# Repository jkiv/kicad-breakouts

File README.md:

# kicad-breakouts

This project contains various breadboard-compatible breakouts for testing and educational purposes.

## Breakouts

### Active Projects

| Device | Manufacturer | Folder | Status | External Links |
| --- | --- | --- | --- | --- |
| ICE40HX8K (caBGA-121) | Lattice | `/boards/ice40hx8k-bg121` | In development... | [[1]](http://www.latticesemi.com/iCE40) |
| LFE5U-* (csBGA-285) | Lattice | `/boards/ecp5-stamp` | In development... | [[2]](http://www.latticesemi.com/ECP5) |
| FT2232H | FTDI | `/boards/ft2232h-ice40` | In development... | [[3]](https://www.ftdichip.com/Products/ICs/FT2232H.htm) |
| ATSAMD21E18A | Atmel | `/boards/atsamd21e18a` | In development... | [[4]](https://www.microchip.com/wwwproducts/en/ATsamd21e18) |

## Dependencies

This project depends on the following KiCad libraries:

* [Digi-Key/digikey-kicad-library](https://github.com/Digi-Key/digikey-kicad-library)
* [jkiv/jkiv-kicad-library](https://github.com/jkiv/jkiv-kicad-library)
* [xesscorp/KiCad-Schematic-Symbol-Libraries](https://github.com/xesscorp/KiCad-Schematic-Symbol-Libraries)

These repositories are set up as git submodules and can be cloned into `hardware/external/` using the following two commands:

    $ git submodule init
    $ git submodule update

## Donations 

Help support this project and others like it by donating:

* XBT: 13zRrs1YDdooUN5WtfXRSDn8KnJdok4qG9

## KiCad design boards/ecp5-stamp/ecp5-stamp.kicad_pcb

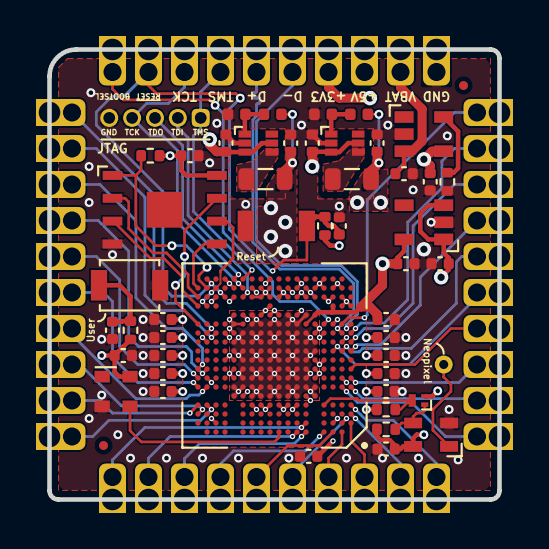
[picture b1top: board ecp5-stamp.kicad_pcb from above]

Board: 4 copper layers, 25.0 x 25.0 mm, 55 parts (0 on the bottom side), 60 nets.

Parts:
C1, C2, C3, C4, C5, C6, C7, C8, C9, C10, C17, C18, C19, C21, C23, C24: 0.1u; C_0402_1005Metric
C11, C12, C13, C14, C20, C22: 4u7; C_0402_1005Metric
C15: 22u; C_0402_1005Metric
C16: 10u; C_0402_1005Metric
D1: SK6805 EC 15; LED_SK6805_PLCC4_2.4x2.7mm_P1.3mm
FID1, FID2: Fiducial; Fiducial_0.5mm_Mask1mm
J1: West; PinHeader_1x10_P2.0mm_Castillated
J2: South; PinHeader_1x10_P2.0mm_Castillated
J3: East; PinHeader_1x10_P2.0mm_Castillated
J4: North; PinHeader_1x10_P2.0mm_Castillated
J5: JTAG; PinHeader_1x05_P1.27mm_Vertical
L1, L2: 2.2u; L_0805_2012Metric
Q1: DMN21D2UFB-7B; Diodes_DFN1006-3
R1, R6: 1k; R_0402_1005Metric
R2, R3: ?k; L_0402_1005Metric
R4, R5: ?; L_0402_1005Metric
R7: 2k; R_0402_1005Metric
R8, R9, R10: 4k7; R_0402_1005Metric
SW1: ~RESET; SW_SPST_B3U-1000P
SW2: ~USER; SW_SPST_B3U-1000P
TP1: NP_OUT; PinHeader_1x01_P1.00mm_Vertical
U1: W25Q128JVS; DFN-8-1EP_6x5mm_P1.27mm_EP2x2mm
U2: MCP73831-2-OT; SOT-23-5
U3: ECP5UM_25_CSFBGA285; BGA-324_18x18_10.0x10.0mm
U4: ASDMB-12.000MHz; Oscillator_SMD_Abracon_ASDMB-4Pin_2.5x2.0mm
U5: TLV73325PDBV; SOT-23-5
U6, U7: TLV62569DRL; SOT-563

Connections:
+1V1: C3.1, C4.1, C15.1, L1.2, R2.1, U3.D8, U3.D9, U3.D10, U3.D11, U3.J4, U3.J5, U3.J14, U3.J15, U3.M4, U3.M15, U3.P7, U3.P9, U3.P10, U3.P11, U3.R10, U3.T5, U3.U6, U3.U8, U3.U12
+2V5: C14.1, C23.1, C24.1, U3.E6, U3.E13, U3.N6, U3.P5, U3.P13, U3.R3, U5.5
+3V3: C2.1, C5.1, C6.1, C7.1, C8.1, C9.1, C10.1, C13.1, C16.1, C17.1, C18.1, J4.4, L2.2, Q1.2, R1.1, R4.1, R6.1, R8.1, R9.1, U1.8, U3.D7, U3.D12, U3.G5, U3.G14, U3.H5, U3.H14, U3.M5, U3.M14, U3.N5, U3.N13, U3.N14, U3.P14, U3.T14, U4.4, U5.1, U5.3
+5V: C11.1, C12.1, C20.1, C21.1, D1.4, J4.3, R10.1, U2.4, U6.3, U6.5, U7.3, U7.5
+BATT: C22.1, J4.2, U2.3
/BOOTSEL: J4.10, U3.N4
/FLASH_CS: R8.2, U1.1, U3.U17
/FLASH_IO0: U1.5, U3.U18
/FLASH_IO1: U1.2, U3.T18
/FLASH_IO2: U1.3, U3.R18
/FLASH_IO3: U1.7, U3.N18
/FLASH_SCK: U1.6, U3.R17, U3.U16
/GPIO_00: J1.1, U3.M17
/GPIO_01: J1.2, U3.M16
/GPIO_02: J1.3, U3.H18
/GPIO_03: J1.4, U3.H17
/GPIO_04: J1.5, U3.G18
/GPIO_05: J1.6, U3.F18
/GPIO_06: J1.7, U3.F17
/GPIO_07: J1.8, U3.C18
/GPIO_08: J1.9, U3.D18
/GPIO_09: J1.10, U3.D17
/GPIO_10: J2.1, U3.B6
/GPIO_11: J2.2, U3.A7
/GPIO_12: J2.3, U3.A6
/GPIO_13: J2.4, U3.A4
/GPIO_14: J2.5, U3.A3
/GPIO_15: J2.6, U3.B2
/GPIO_16: J2.7, U3.A2
/GPIO_17: J2.8, U3.B1
/GPIO_18: J2.9, U3.C1
/GPIO_19: J2.10, U3.D1
/GPIO_20: J3.1, U3.F2
/GPIO_21: J3.2, U3.F1
/GPIO_22: J3.3, U3.G1
/GPIO_23: J3.4, U3.H1
/GPIO_24: J3.5, U3.K3
/GPIO_25: J3.6, U3.K2
/GPIO_26: J3.7, U3.K1
/GPIO_27: J3.8, U3.L1
/GPIO_28: J3.9, U3.M1
/GPIO_29: J3.10, U3.N2
/JTAG_TCK: J4.8, J5.4, U3.U13
/JTAG_TDI: J5.2, U3.T13
/JTAG_TDO: J5.3, U3.V14
/JTAG_TMS: J4.7, J5.1, U3.V13
/NP_SDI: D1.3, Q1.1, R10.2
/NP_SDI_LV: Q1.3, R9.2, U3.D4
/NP_SDO: D1.1, TP1.1
/REF_CLK: U3.A9, U4.3
/SW_1V1: L1.1, U6.4
/SW_3V3: L2.1, U7.4
/USB_D+: J4.6, U3.M2
/USB_D-: J4.5, U3.N1
/~RESET: C1.1, J4.9, R1.2, SW1.2, U3.T15, U3.V17
/~USER: C19.1, R6.2, SW2.2
GND: C1.2, C2.2, C3.2, C4.2, C5.2, C6.2, C7.2, C8.2, C9.2, C10.2, C11.2, C12.2, C13.2, C14.2, C15.2, C16.2, C17.2, C18.2, C19.2, C20.2, C21.2, C22.2, C23.2, C24.2, D1.2, J4.1, J5.5, R3.2, R5.2, R7.2, SW1.1, SW2.1, U1.4, U2.2, U3.B3, U3.B16, U3.E5, U3.E7, U3.E8, U3.E9, U3.E10, U3.E11, U3.E12, U3.E14, U3.F5, U3.F6, U3.F7, U3.F8, U3.F9, U3.F10, U3.F11, U3.F12, U3.F13, U3.F14, U3.G2, U3.G6, U3.G7, U3.G8, U3.G9, U3.G10, U3.G11, U3.G12, U3.G13, U3.G17, U3.H6, U3.H7, U3.H8, U3.H9, U3.H10, U3.H11, U3.H12, U3.H13, U3.J6, U3.J7, U3.J8, U3.J9, U3.J10, U3.J11, U3.J12, U3.J13, U3.K5, U3.K6, U3.K7, U3.K8, U3.K9, U3.K10, U3.K11, U3.K12, U3.K13, U3.K14, U3.L2, U3.L5, U3.L6, U3.L7, U3.L8, U3.L9, U3.L10, U3.L11, U3.L12, U3.L13, U3.L14, U3.L17, U3.M6, U3.M7, U3.M8, U3.M9, U3.M10, U3.M11, U3.M12, U3.M13, U3.N7, U3.N8, U3.N9, U3.N10, U3.N11, U3.N12, U3.P6, U3.P8, U3.P12, U3.R1, U3.R2, U3.T2, U3.T3, U3.T4, U3.T6, U3.T7, U3.T8, U3.T9, U3.T10, U3.T11, U3.T12, U3.T16, U3.U2, U3.U3, U3.U4, U3.U5, U3.U7, U3.U9, U3.U10, U3.U11, U3.U14, U3.V4, U3.V7, U3.V10, U3.V15, U4.2, U5.2, U6.2, U7.2
unnamed: R2.2, R3.1, U6.1
unnamed: R4.2, R5.1, U7.1
unnamed: R7.1, U2.5

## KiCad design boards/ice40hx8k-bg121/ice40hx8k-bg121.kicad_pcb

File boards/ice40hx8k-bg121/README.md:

# ice40hx8k-bg121 Breakout Board

## About

This is a breadboardable breakout board for a Lattice iCE40HX8K FPGA.

* Four IO banks with 32 exposed IOs
  * 12 + 4 breadboardable IO
  * 8 + 8 IO via 2.54mm headers
  * Eight on-board LEDs (Bank D)
* Settable VIO for IO Banks A, B, and D.
* 12-pin PMOD compatible pinout for IO banks B and D.
* 6-pin PMOD compatible pinout for IO bank C.
* On-board 2Mbit flash memory.
* On-board 12MHz clock source.
* On-board reset button.

*This board does **not** contain programming circuitry. The [`ft2232h-ice40` breakout](https://github.com/jkiv/kicad-breakouts/tree/main/boards/ft2232h-ice40) is intended to provide the programming circuitry for this board.*

## Rationale

This board began with the intent to provide a breadboardable FPGA for educational purposes.

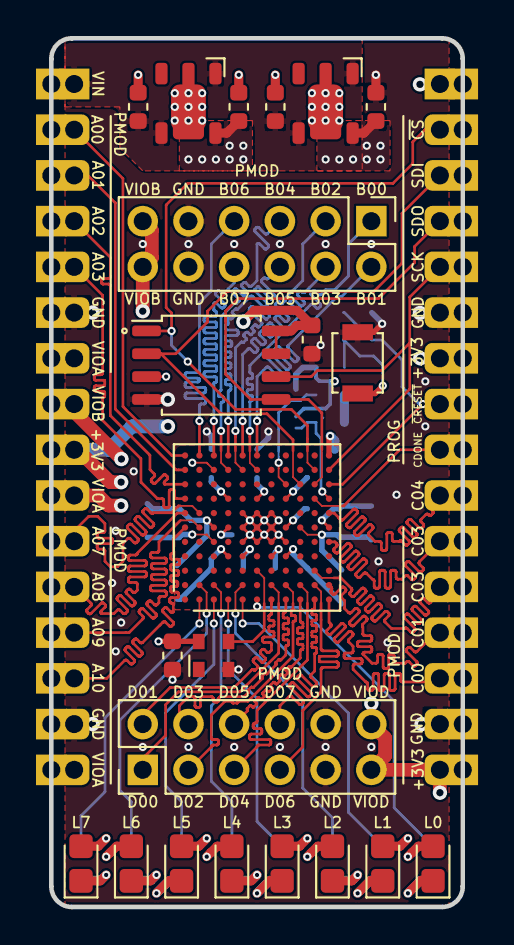
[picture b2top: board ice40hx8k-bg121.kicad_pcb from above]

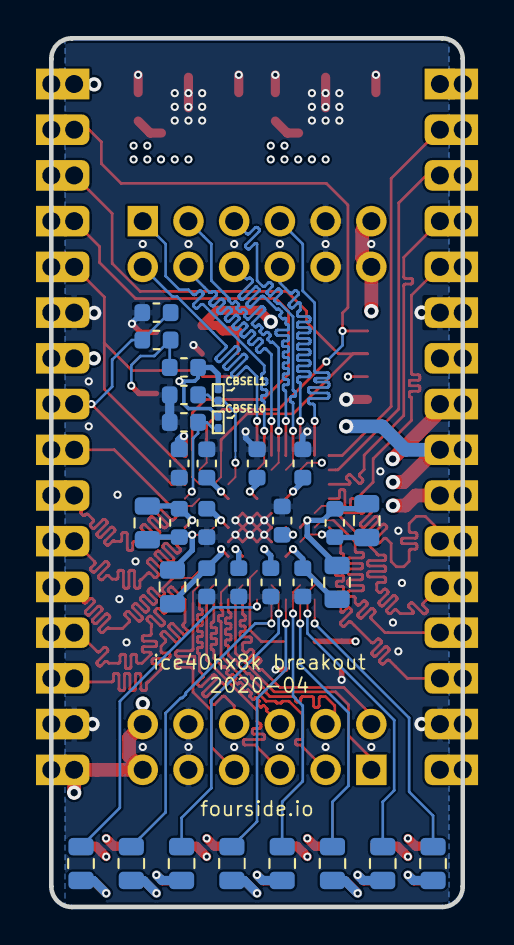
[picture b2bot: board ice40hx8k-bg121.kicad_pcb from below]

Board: 4 copper layers, 22.9 x 48.3 mm, 55 parts (33 on the bottom side), 65 nets.

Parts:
C1, C2, C3, C4: 4.7uF; C_0603_1608Metric
C5, C6, C7, C8, C10, C11, C12, C13, C15, C16, C17, C18, C19, C20, C21: 0.1u; C_0603_1608Metric
C9, C14: 10u; C_0805_2012Metric
D3: L7; LED_0805_2012Metric_Castellated
D4: L6; LED_0805_2012Metric_Castellated
D5: L5; LED_0805_2012Metric_Castellated
D6: L4; LED_0805_2012Metric_Castellated
D7: L3; LED_0805_2012Metric_Castellated
D8: L2; LED_0805_2012Metric_Castellated
D9: L1; LED_0805_2012Metric_Castellated
D10: L0; LED_0805_2012Metric_Castellated
J1, J2: Conn_01x16; PinHeader_1x16_P2.54mm_Vertical
J3, J4: Conn_02x06_Odd_Even; PinHeader_2x06_P2.54mm_Vertical
JP1: CBSEL1; J_NO_0201_0603Metric
JP2: CBSEL0; J_NO_0201_0603Metric
R1, R2: 10k; R_0603_1608Metric
R3, R4, R5, R6, R7, R8, R9, R10: 220R; R_0805_2012Metric
R11, R13: 100R; R_0805_2012Metric
R12, R14: 1k; R_0603_1608Metric
SW1: B3U-1000P; SW_SPST_B3U-1000P
U1: AP7361C-33Y5-13; SOT89-5
U2: AP7361C-12Y5-13; SOT89-5
U3: iCE40HX8K-BG121(121-Ball_caBGA); BGA-121_9.0x9.0mm_Layout11x11_P0.8mm_Ball0.4mm_Pad0.35mm_NS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
U4: LE25U20AMB; SOIC-8_5.275x5.275mm_P1.27mm
U5: ASDMB-xxxMHz; Oscillator_SMD_Abracon_ASDMB-4Pin_2.5x2.0mm

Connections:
+1V2: C4.1, C5.2, C6.2, C7.2, C8.2, R11.1, R13.1, U2.5, U3.D4, U3.D8, U3.H4, U3.H8
+5V: C1.1, C3.1, J1.1, U1.1, U1.4, U2.1, U2.4
/ICE40HX8K/FPGA_CLK: U3.F3, U5.3
/ICE40HX8K/GNDPLL0: C9.1, C10.1, U3.L6
/ICE40HX8K/GNDPLL1: C14.1, C15.1, U3.C5
/ICE40HX8K/VCCPLL0: C9.2, C10.2, R11.2, U3.J6
/ICE40HX8K/VCCPLL1: C14.2, C15.2, R13.2, U3.C6
CBSEL0: JP1.1, R1.1, U3.L8
CBSEL1: JP2.2, R2.1, U3.H9
CDONE: J2.9, U3.K8
GND: C1.2, C2.2, C3.2, C4.2, C5.1, C6.1, C7.1, C8.1, C11.1, C12.1, C13.1, C16.1, C17.1, C18.1, C19.1, C20.2, C21.1, J1.6, J1.15, J2.6, J2.15, J3.9, J3.10, J4.9, J4.10, R1.2, R2.2, SW1.2, U1.2, U2.2, U3.E5, U3.E6, U3.E7, U3.F5, U3.F6, U3.F7, U3.G5, U3.G6, U3.G7, U3.H5, U4.4, U5.2
IO_A00: J1.2, U3.A11
IO_A01: J1.3, U3.A10
IO_A02: J1.4, U3.A9
IO_A03: J1.5, U3.A8
IO_A04: J1.11, U3.B7
IO_A05: J1.12, U3.A7
IO_A06: J1.13, U3.B6
IO_A07: J1.14, U3.A6
IO_B00: J4.1, U3.F10
IO_B01: J4.2, U3.F11
IO_B02: J4.3, U3.E10
IO_B03: J4.4, U3.E11
IO_B04: J4.5, U3.D10
IO_B05: J4.6, U3.D11
IO_B06: J4.7, U3.B11
IO_B07: J4.8, U3.C11
IO_C00: J2.14, U3.L1
IO_C01: J2.13, U3.L2
IO_C02: J2.12, U3.K3
IO_C03: J2.11, U3.L5
IO_C04: J2.10, U3.L7
IO_D00: J3.1, U3.G2
IO_D01: J3.2, U3.G1
IO_D02: J3.3, U3.H2
IO_D03: J3.4, U3.H1
IO_D04: J3.5, U3.J2
IO_D05: J3.6, U3.J1
IO_D06: J3.7, U3.K2
IO_D07: J3.8, U3.K1
IO_L0: R10.1, U3.F1
IO_L1: R9.1, U3.E1
IO_L2: R8.1, U3.E2
IO_L3: R7.1, U3.D1
IO_L4: R6.1, U3.C2
IO_L5: R5.1, U3.C1
IO_L6: R4.1, U3.B2
IO_L7: R3.1, U3.B1
unnamed: D3.1, R3.2
unnamed: D4.1, R4.2
unnamed: D5.1, R5.2
unnamed: D6.1, R6.2
unnamed: D7.1, R7.2
unnamed: D8.1, R8.2
unnamed: D9.1, R9.2
unnamed: D10.1, R10.2
unnamed: R12.1, R14.2, SW1.1
PROG_CRESET_B: C20.1, J2.8, R12.2, U3.L9
PROG_SCK: J2.5, U3.L10, U4.6
PROG_SDI: J2.3, U3.J9, U4.2
PROG_SDO: J2.4, U3.K9, U4.5
PROG_SS_B: J2.2, U3.K10, U4.1
VCCIO_A: C11.2, J1.7, J1.10, J1.16, U3.D6
VCCIO_B: C12.2, J1.8, J4.11, J4.12, U3.F8
VCCIO_C: C2.1, C13.2, C16.2, C17.2, C18.2, C19.2, C21.2, D3.2, D4.2, D5.2, D6.2, D7.2, D8.2, D9.2, D10.2, J1.9, J2.1, J2.7, J2.16, J3.11, J3.12, JP1.2, JP2.1, R14.1, U1.5, U3.C10, U3.E4, U3.G4, U3.H6, U3.L11, U4.3, U4.7, U4.8, U5.4

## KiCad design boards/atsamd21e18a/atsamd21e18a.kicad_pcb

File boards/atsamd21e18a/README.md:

# atsamd21e18a Breakout Board

## About

This is a breadboardable breakout board for the Atmel SAMD21 32-bit ARM microcontroller.

* 32-pin Atmel SAMD21 microcontroller (`atsamd21e18a`).
* 18 IOs exposed.
* Direct USB interface.
* 10-pin 1.27mm SWD header.
  * SWD signals exposed via 2.54mm.
* On-board reset button.
* On-board 32.768 kHz crystal.

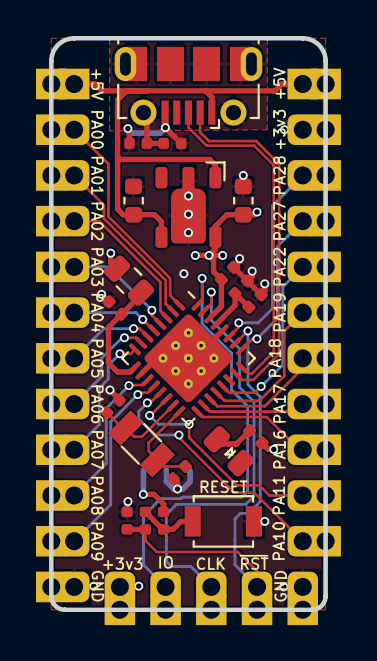
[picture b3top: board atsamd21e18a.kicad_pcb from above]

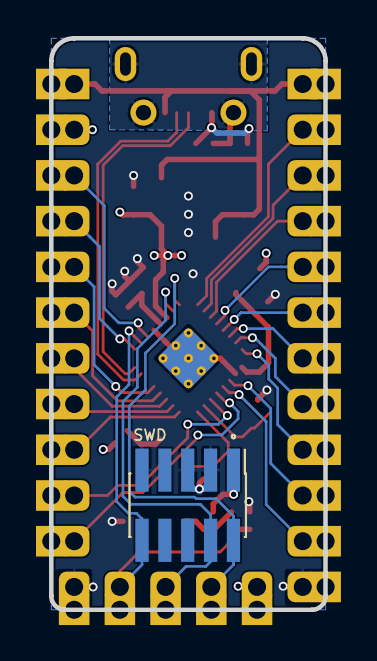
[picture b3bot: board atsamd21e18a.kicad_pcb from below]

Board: 4 copper layers, 15.2 x 31.8 mm, 25 parts (3 on the bottom side), 34 nets.

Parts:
C1, C6: 4.7u; C_0603_1608Metric
C2: 1u; C_0402_1005Metric
C3, C4, C5, C9: 0.1u; C_0402_1005Metric
C7, C8: 22p; C_0402_1005Metric
C10: 0.01u; C_0402_1005Metric
D1: PWR_LED; LED_0805_2012Metric
FB1: FB; L_0805_2012Metric
J1: USB_B_Micro; USB_Micro-B_Molex-105017-0001
J2: A; PinHeader_1x12_P2.54mm_Vertical
J3: B; PinHeader_1x12_P2.54mm_Vertical
J4: SWD_1.27; PinHeader_2x05_P1.27mm_Vertical_SMD
J5: SWD_2.54; PinHeader_1x04_P2.54mm_Vertical
R1: 4k7; R_0402_1005Metric
R2, R3: 1k; R_0402_1005Metric
R4: 100k; R_0402_1005Metric
SW1: RESET; SW_SPST_B3U-1000P
U1: AP7361C_SOT-89-5; SOT89-5
U2: ATSAMD21E; QFN-32-1EP_5x5mm_P0.5mm_EP3.6x3.6mm_ThermalVias
Y1: ABS07-32.768KHZ; Crystal_SMD_3215-2Pin_3.2x1.5mm

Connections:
+3V3: C5.2, C6.1, FB1.1, J3.2, J4.1, J5.1, R1.1, R3.1, U1.5, U2.30
+5V: C1.1, J1.1, J2.1, J3.1, U1.1, U1.4
/PA00: J2.2, U2.1
/PA01: J2.3, U2.2
/PA02: J2.4, U2.3
/PA03: J2.5, U2.4
/PA04: J2.6, U2.5
/PA05: J2.7, U2.6
/PA06: J2.8, U2.7
/PA07: J2.9, U2.8
/PA08: J2.10, U2.11
/PA09: J2.11, U2.12
/PA10: J3.11, U2.13
/PA11: J3.10, U2.14
/PA14: C7.1, U2.15, Y1.1
/PA15: C8.1, U2.16, Y1.2
/PA16: J3.9, U2.17
/PA17: J3.8, U2.18
/PA18: J3.7, U2.19
/PA19: J3.6, U2.20
/PA22: J3.5, U2.21
/PA27: J3.4, U2.25
/PA28: J3.3, U2.27
/SWD_CLK: J4.4, J5.3, U2.31
/SWD_IO: J4.2, J5.2, U2.32
/USB_D+: J1.3, U2.24
/USB_D-: J1.2, U2.23
/USB_SHIELD: C10.2, J1.6, R4.2
/VDDANA: C4.2, FB1.2, U2.9
/VDDCORE: C2.2, C3.2, U2.29
/~RESET: C9.1, J4.10, J5.4, R2.2, U2.26
GND: C1.2, C2.1, C3.1, C4.1, C5.1, C6.2, C7.2, C8.2, C9.2, C10.1, D1.1, J1.5, J2.12, J3.12, J4.3, J4.5, J4.9, R4.1, SW1.2, U1.2, U2.10, U2.28, U2.33
unnamed: D1.2, R1.2
unnamed: R2.1, R3.2, SW1.1

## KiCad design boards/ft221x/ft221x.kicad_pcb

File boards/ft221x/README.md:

# ft221x Breakout Board

## About

This is a breadboardable breakout for the USB-to-SPI [FT221X](https://www.ftdichip.com/Products/ICs/FT221X.html) chip.

## Rationale

This board was originally intended to explore whether or not the FT221X could be used as a less expensive alternative to the [FT2232H](https://www.ftdichip.com/Products/ICs/FT2232H.html) chip, for the purpose of programming [Lattice iCE40](http://www.latticesemi.com/iCE40) devices with [iceprog](https://github.com/YosysHQ/icestorm/tree/master/iceprog). However, unlike the standard FT2232H solution, the `CDONE` and `~CRESET` signals would not be available.

I ended up making the [ft2232h-ice40](https://github.com/jkiv/kicad-breakouts/tree/main/boards/ft2232h-ice40) breakout for this purpose instead.

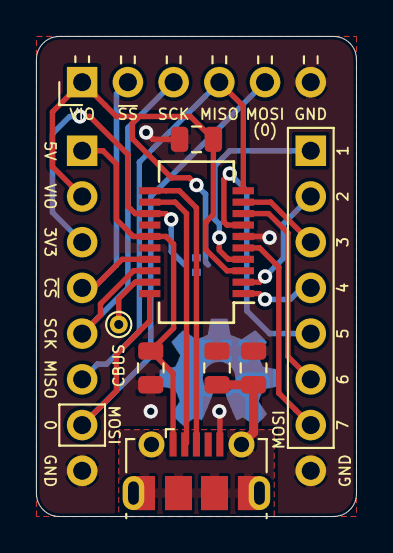
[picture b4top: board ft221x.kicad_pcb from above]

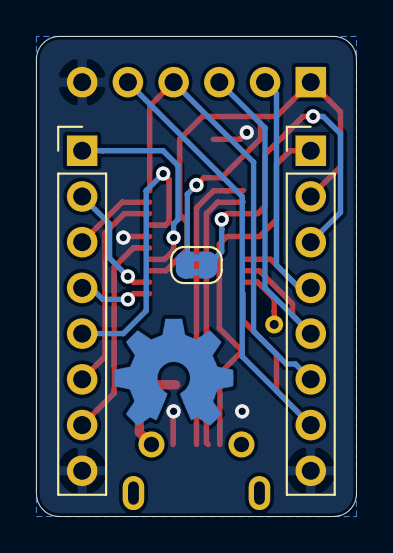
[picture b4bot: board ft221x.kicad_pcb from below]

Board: 2 copper layers, 17.8 x 26.7 mm, 11 parts (3 on the bottom side), 19 nets.

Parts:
C1: 10n; C_0805_2012Metric
C2, C3: 0.1u; C_0805_2012Metric
CBUS: CBUS; TestPoint_THTPad_D1.0mm_Drill0.5mm
J1: USB_B_Micro; USB_Micro-B_Molex-105017-0001
J2: BREADBOARD_A; PinHeader_1x08_P2.54mm_Vertical
J3: BREADBOARD_B; PinHeader_1x08_P2.54mm_Vertical
J4: BREAKOUT_SPI1; PinHeader_1x06_P2.54mm_Horizontal
JP1: USE_3v3OUT; SolderJumper-2_P1.3mm_Bridged2Bar_RoundedPad1.0x1.5mm
R1: 100k; R_0805_2012Metric
U1: FT221XS; SSOP-20_3.9x8.7mm_P0.635mm

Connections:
/3v3OUT: J2.3, JP1.1, U1.13
/CBUS: CBUS.1, U1.19
/MISO: J2.6, J4.4, U1.10
/MOSI0: J2.7, J4.5, U1.20
/MOSI1: J3.1, U1.4
/MOSI2: J3.2, U1.2
/MOSI3: J3.3, U1.9
/MOSI4: J3.4, U1.1
/MOSI5: J3.5, U1.7
/MOSI6: J3.6, U1.8
/MOSI7: J3.7, U1.5
/SCK: J2.5, J4.3, U1.18
/USB_D+: J1.3, U1.11
/USB_D-: J1.2, U1.12
/VCCIO: C3.2, J2.2, J4.1, JP1.2, U1.3
/~CS: J2.4, J4.2, U1.17
GND: C1.1, C2.1, C3.1, J1.5, J2.8, J3.8, J4.6, R1.2, U1.6, U1.16
unnamed: C1.2, J1.6, R1.1
VBUS: C2.2, J1.1, J2.1, U1.15

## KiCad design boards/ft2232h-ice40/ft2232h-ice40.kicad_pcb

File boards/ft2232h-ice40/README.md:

# ft2232h-ice40 Breakout Board

## About

This board breaks out the signals required to program a Lattice ice40 FPGA via USB using [`iceprog`](https://github.com/YosysHQ/icestorm/tree/master/iceprog).

## Rationale

The [`ice40hx8k-bg121` breakout board](https://github.com/jkiv/kicad-breakouts/tree/main/boards/ice40hx8k-bg121) does not contain the circuitry required to program either the on-board FLASH chip, or the FPGA itself.

Typically, a FT2232H is used to provide the interface for programming these devices, e.g. via the [`iceprog`](https://github.com/YosysHQ/icestorm/tree/master/iceprog) software.

Instead of integrating the rather expensive FT2232H onto each small, ice40 breakout board, this board is inteded to be reused against multiple ice40 breakout boards.

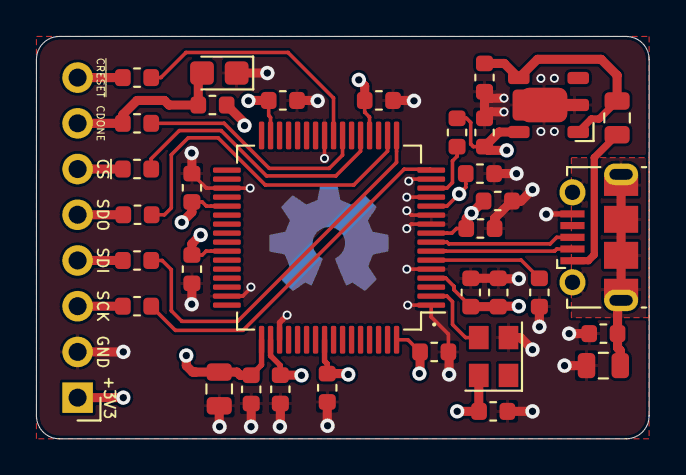
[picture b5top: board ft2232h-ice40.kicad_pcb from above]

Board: 4 copper layers, 34.0 x 22.4 mm, 35 parts (0 on the bottom side), 23 nets.

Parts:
C1, C4, C8, C13: 4.7u; C_0603_1608Metric
C2: 0.01u; C_0603_1608Metric
C3, C5, C6, C7, C9, C10, C11, C14, C15, C16, C17, C18: 0.1u; C_0603_1608Metric
C12: 10u; C_0805_2012Metric
D1: CDONE; LED_0805_2012Metric_Castellated
FB1: FB; L_0805_2012Metric
J1: USB_B_Micro; USB_Micro-B_Molex-105017-0001
J2: Conn_01x08; PinHeader_1x08_P2.54mm_Horizontal
R1: 100k; R_0805_2012Metric
R2: 1k; R_0603_1608Metric
R3, R4: 10k; R_0603_1608Metric
R5, R6, R7, R8, R9, R10: 22R; R_0603_1608Metric
U1: AP7361C_SOT-89-5; SOT89-5
U2: FT2232H; LQFP-64_10x10mm_P0.5mm
X1: ASEM1-12.000MHZ; Oscillator_SMD_Abracon_ASE-4Pin_3.2x2.5mm

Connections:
+1V8: C12.1, C14.1, C15.1, C17.1, C18.1, U2.12, U2.37, U2.49, U2.64
+3V3: C3.1, C4.1, C5.1, C6.1, C7.1, C8.1, C9.1, C10.1, C11.1, C13.1, C16.1, J2.1, R2.1, R4.2, U1.5, U2.4, U2.9, U2.20, U2.31, U2.42, U2.50, U2.56, X1.4
+5V: C1.1, FB1.1, U1.1, U1.4
/CDONE: D1.2, J2.7, R2.2, R9.1
/CLK_12MHz: U2.2, X1.3
/CRESET_B: J2.8, R10.1
/MISO: J2.5, R7.1
/MOSI: J2.4, R6.1
/SCK: J2.3, R5.1
/SHIELD: C2.1, J1.6, R1.1
/USB_D+: J1.3, U2.8
/USB_D-: J1.2, U2.7
/VBUS: FB1.2, J1.1
/~CS: J2.6, R8.1
GND: C1.2, C2.2, C3.2, C4.2, C5.2, C6.2, C7.2, C8.2, C9.2, C10.2, C11.2, C12.2, C13.2, C14.2, C15.2, C16.2, C17.2, C18.2, D1.1, J1.5, J2.2, R1.2, R3.2, U1.2, U2.1, U2.5, U2.10, U2.11, U2.13, U2.15, U2.25, U2.35, U2.47, U2.51, X1.2
unnamed: R3.1, U2.6
unnamed: R4.1, U2.14
unnamed: R5.2, U2.16
unnamed: R6.2, U2.17
unnamed: R7.2, U2.18
unnamed: R8.2, U2.21
unnamed: R9.2, U2.23
unnamed: R10.2, U2.24

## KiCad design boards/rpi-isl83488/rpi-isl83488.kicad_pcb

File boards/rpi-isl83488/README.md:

# ISL83488/90 adapter for Raspberry Pi

This board is a UART to full-duplex RS485 adapter for the Raspberry Pi which
uses the Renesas ISL83488 (or ISL83490) to provide the signal conversion.

The board provides a 0.1" (2.54mm) edge recepticle to plug into the top 2x5
pins of the Raspberry Pi header.

The board uses the +3v3 provided by the Raspberry Pi for power, pins 6 and
9 for GND, and pins 8 and 10 for TX and RX respectively.

Points labelled RX and TX on this board are with respect to the Raspberry
Pi.

The full-duplex RS485 output is available via a 4-pin JST-GH connector.

Also, the RX and TX provided by the Raspberry Pi are available
via an additional 2-pin 0.1" (2.54mm) header.

This board was originally inteded to be used with the
[`jkiv/icepool-board`](https://github.com/jkiv/icepool-board) project.

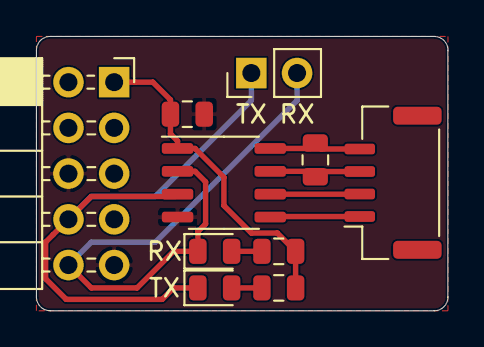
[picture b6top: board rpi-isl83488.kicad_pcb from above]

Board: 2 copper layers, 22.9 x 15.2 mm, 10 parts (0 on the bottom side), 10 nets.

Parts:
C1: 0.1u; C_0805_2012Metric
D1: TX; LED_0805_2012Metric
D2: RX; LED_0805_2012Metric
J1: RPi; PinSocket_2x05_P2.54mm_Horizontal
J2: JST-GH; JST_GH_SM04B-GHS-TB_1x04-1MP_P1.25mm_Horizontal
J3: SERIAL; PinHeader_1x02_P2.54mm_Vertical
R1: 120R; R_0805_2012Metric
R2, R3: 1k; R_0805_2012Metric
U1: ISL83488; SO-8_3.9x4.9mm_P1.27mm

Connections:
+3V3: C1.1, J1.1, R2.2, R3.2, U1.1
/RX: D2.1, J1.10, J3.2, U1.2
/RX+: J2.4, R1.2, U1.8
/RX-: J2.3, R1.1, U1.7
/TX: D1.1, J1.8, J3.1, U1.3
/TX+: J2.2, U1.6
/TX-: J2.1, U1.5
GND: C1.2, J1.6, J1.9, U1.4
unnamed: D1.2, R2.1
unnamed: D2.2, R3.1

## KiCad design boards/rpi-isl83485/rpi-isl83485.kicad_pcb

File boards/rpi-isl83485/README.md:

# ISL83485 adapter for Raspberry Pi

This board is a UART to half-duplex RS485 adapter for the Raspberry Pi which
uses the Renesas ISL83485 to provide the signal conversion.

The board provides a 0.1" (2.54mm) edge recepticle to plug into the top 2x5
pins of the Raspberry Pi header.

The board uses the +3v3 provided by the Raspberry Pi for power, pins 6 and
9 for GND, pin 7 for ~read enable/drive enable (~RE), and pins 8 and 10 for
TX and RX respectively.

Points labelled RX and TX on this board are with respect to the Raspberry
Pi.

The half-duplex RS485 signal is available via a 2-pin JST-GH connector.

Also, the ~RE, RX and TX provided by the Raspberry Pi are available
via an additional 2-pin 0.1" (2.54mm) header.

This board was originally inteded to be used with the
[`jkiv/icepool-board`](https://github.com/jkiv/icepool-board) project.

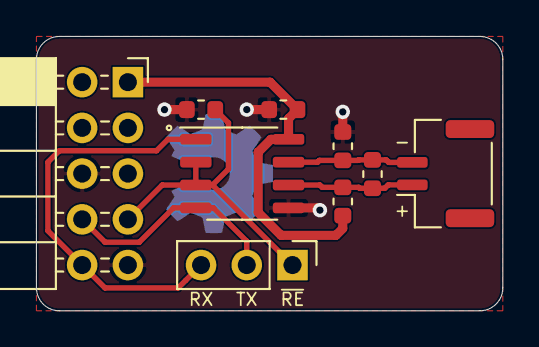
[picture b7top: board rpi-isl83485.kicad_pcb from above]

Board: 2 copper layers, 25.9 x 15.2 mm, 9 parts (0 on the bottom side), 7 nets.

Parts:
C1: 0.1u; C_0603_1608Metric
J1: RPi; PinSocket_2x05_P2.54mm_Horizontal
J2: Conn_01x03; PinHeader_1x03_P2.54mm_Vertical
J3: JST-GH; JST_GH_SM02B-GHS-TB_1x02-1MP_P1.25mm_Horizontal
R2, R5: Rb; R_0603_1608Metric
R3: 10k; R_0603_1608Metric
R4: Rt; R_0603_1608Metric
U1: ISL83485; SO-8_3.9x4.9mm_P1.27mm

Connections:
+3V3: C1.1, J1.1, R2.1, U1.8
/DS+: J3.1, R2.2, R4.1, U1.6
/DS-: J3.2, R4.2, R5.1, U1.7
/RxD: J1.10, J2.3, U1.1
/TxD: J1.8, J2.2, U1.4
/~RE: J1.7, J2.1, R3.1, U1.2, U1.3
GND: C1.2, J1.6, J1.9, R3.2, R5.2, U1.5

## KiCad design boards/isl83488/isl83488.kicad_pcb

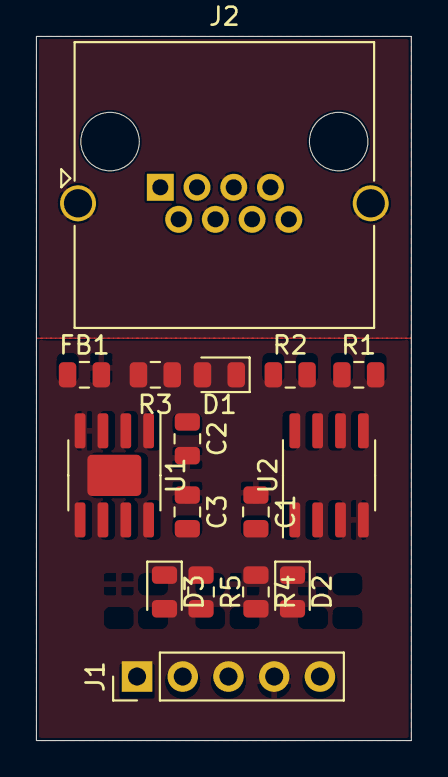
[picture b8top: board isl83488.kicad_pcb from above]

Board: 4 copper layers, 20.8 x 39.1 mm, 16 parts (0 on the bottom side), 14 nets, no tracks yet.

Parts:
C1: 0.1u; C_0805_2012Metric
C2, C3: 4.7u; C_0805_2012Metric
D1, D2, D3: LTST-C171GKT; LED_0805_2012Metric
FB1: Ferrite; L_0805_2012Metric
J1: Conn_01x05; PinHeader_1x05_P2.54mm_Vertical
J2: 8P8C_Shielded; RJ45_Amphenol_RJHSE5380
R1: 120R; R_0805_2012Metric
R2: OMIT; R_0805_2012Metric
R3: 55R; R_0805_2012Metric
R4, R5: 140R; R_0805_2012Metric
U1: AP7361C_SO-8EP; SOIC-8-1EP_3.9x4.9mm_P1.27mm_EP2.29x3mm
U2: ISL83488; SOIC-8_3.9x4.9mm_P1.27mm

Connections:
+3V3: C1.2, C2.1, J1.5, R3.2, U1.1, U2.1
+5V: C3.2, J1.1, U1.2, U1.8
/GND_SH: FB1.1, J2.4, J2.5, J2.7, J2.8, J2.SH
/RX: J1.2, R5.2, U2.2
/RX+: J2.2, R2.1, U2.8
/RX-: J2.1, R2.2, U2.7
/TX: J1.3, R4.2, U2.3
/TX+: J2.6, R1.2, U2.5
/TX-: J2.3, R1.1, U2.6
GND: C1.1, C2.2, C3.1, D1.1, D2.1, D3.1, FB1.2, J1.4, U1.4, U2.4
unnamed: D1.2, R3.1
unnamed: D2.2, R4.1
unnamed: D3.2, R5.1
unnamed: U1.3, U1.5, U1.6, U1.7

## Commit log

2019-12-06 Initial commit.
2019-12-06 Fixing markdown table in README.md
2019-12-06 Unformatting header in README.md
2019-12-09 Schematic and Layout: The Beginning
2019-12-09 Added README.md content.
2019-12-11 Started putting down traces.
    Still need to do C and differential pairs D.
2020-01-15 Starting ISL83488 breakout
2020-02-03 Added Raspberry Pi 3 header for ISL83485.
2020-02-04 No longer interested in ISL83488.
    Layout for ICE40HX8K-BG121 -- just need power.
2020-02-05 Fanout of BGA, and power.
2020-03-02 Send to fab.
2020-04-04 Updated LDOs to SOT89-5 footprint.
2020-05-02 Added RPi header for full-duplex ISL83488/90 chip.
2020-05-03 Fixed programming CRESET_B/SPI_SS_B. Fixed ground connections. Fixed 2V5.
2020-05-03 Added xess library to .gitignore.
2020-05-04 Added FT221X (USB to SPI) breakout board.
2020-05-20 Silkscreen fixes. Moved C19.
2020-05-20 Removed U3 designator.
2020-05-21 Created atsamd21e18a breakout.
2020-05-23 Reduced board width. Reduced size of passives as a result.
2020-05-23 Moved atsamd21e18a to '4layer'.
2020-05-23 Added atsamd21e18a-2layer
2020-05-23 Replaced 3225 crystal with 3215 on atsamd21e18a
2020-05-29 Probably going to keep the 4-layer atsamd21e18a board. Renamed.
2020-05-29 Fixed errors in main README. Added boards.
    Accidentally committed changes to ice40hx8k-bg121 and atsamd21e18a
    boards.
    The ice40hx8k-bg121 changes include adding access to CBSEL0/1 and
    rerouting IO.
    The atsamd21e18a changes include rerouting IO to prioritize USB
    D+/- routing.
2020-05-29 Added links to main README. Removed TODO.
2020-05-29 Minor main README changes.
2020-05-29 For whatever reason, updated ISL83485.
2020-05-29 Removed reference to "Raspberry Pi 3". Now just Raspberry Pi.
2020-05-29 Removed reference to "Raspberry Pi 3". Now just Raspberry Pi. (2)
2020-05-29 Updated ISL83488 README.
2020-05-29 Updated ISL83485/88 README's for clarity.
2020-05-30 Techincally, reworked routing. Finished 3v3 and SOF 1 kHz routing.
2020-06-01 Created FT2232H board for ice40 programming
2020-06-03 Fixed typos in README.
2020-06-03 Added FT2232H breakout for programming /boards/ice40hx8k-bg121/
2020-06-03 Added ft2232h-ice40 to README
2020-06-03 Fixed FT2232 link.
2020-06-27 Updates to atsamd21e18a fp-info-cache. (Unsure.)
2020-06-27 Added gerbers and HTML BOM to atsamd21e18a.
2020-06-27 Changes to ft221x PCB. (Unsure.)
2020-06-27 Added HTML BOM and gerbers for ft221x.
2020-06-27 Added HTML BOM and gerbers to ft2232h-ice40.
2020-06-27 Added HTML BOM and gerbers to ice40hx8k-bg121.
2020-06-27 Changes to ft2232h-ice40. (Unsure.)
2020-06-27 Changes to ice40hx8k-bg121 PCB. (Unsure.)
2020-06-27 Changes to rpi-isl83488 PCB. (Unsure.)
2020-06-27 Added HTML BOM and gerbers to rpi-isl83488.
2020-06-27 Added gerbers for atsamd21e18a (2-layer).
2020-06-27 Added bom/ and gerber/ to .gitignore.
2020-06-27 Removed "R1" silkscreen label.
    Addresses issue #4.
    Also adjusted CBUS silkscreen label.
2020-06-27 Added README for the ft221x.
2020-06-27 Figuring out embedded images in github markdown.
2020-06-27 Using raw github URL for image in ft221x README.
2020-06-27 Removed ft221x.sch-bak.
2020-06-27 Updated ft221x README.
2020-06-27 Updated HTML BOM with fixed silkscreen (issue #4).
    Updated name of BOM to fit convention.
2020-06-27 Added README and render for ft2232h-ice40.
    Addresses issue #1.
2020-06-27 Fixed redundant use of 'instead' in ft2232h-ice40 README.
2020-06-27 Swapped position of image in READMEs.
2020-06-27 Removed sch-bak's from ice40hx8k-bg121.
2020-06-27 Fixed typo on IO Bank D's silkscreen.
2020-06-27 Added README for ice40hx8k-bg121 breakout.
2020-06-27 Removed sch-bak from atsamd21e18a.
2020-06-27 Added README to atsamd21e18a.
    Addresses issue #1.
2020-06-27 Added profile image of atsamd21e18a.
    Addresses issue #1.
2020-06-27 Consistent periods in atsamd21e18a README
2020-07-07 Removed solder jumpers for USB SOF/ID and SWD 3v3.
    Fixes issue #6. Fixes issue #8.
2020-07-07 Added filter to USB. Added USB shield zone to F.Cu and B.Cu.
    Fixes issue #7.
2020-07-07 Removed atsamd21e18a-2layer. Not used.
2020-07-07 Removed atsamd21e18a-2layer reference from README.
2020-09-22 Version 2020-04 looks good. Next: panelize.
2020-10-13 Connected VREGIN to +3v3 with 0.1u filter cap.
2020-10-13 Reduced FT2232H solderpaste area by 20%.
2020-10-13 Minor tweaks to signal layout.
2020-10-13 Removed off-board silkscreen for horizontal pin header.
2020-10-13 Updated version info on backside of board.
2020-10-13 Revert "Updated version info on backside of board."
    This reverts commit 1f51933b87c9f3e20d21da3a8fb08a06faebd8ba.
2020-11-10 [ft2232h-ice40] Passes DRC.
2020-11-10 [ice40hx8k-bg121] Updated design rules. Passes DRC.
    Updated design rules. Adjusted soldermask clearance ratio.
2020-11-10 Updated sheet info, gerbers, BOMs.
    * ft2232h-ice40
    * ice40hx8k-bg121 breakout
    * atsamd21e18a
2020-11-10 Updated soldermask clearance, DRC rules, gerbers, and BOMs.
    * ft221
    * atsamd21e18a
2020-11-10 Updated 3D renders.
    * atsamd21e18a
    * ft221x
    * ft2232h-ice40
    * ice40hx8k-bg121
2020-11-10 Split breakouts into "Active" and "Inactive" in README.
    Addresses issue #10.
2020-11-10 [ice40hx8k-bg121] Added mention of on-board FLASH memory to README.
    Addresses issue #5.
2020-11-10 Relative image links. Scaled images by 50%
    * atsamd21e18a
    * ft221x
    * ft2232h-ice40
    * ice04hx8k-bg121
2020-12-22 N.O. Jumpers for PA14 and PA15.
2020-12-22 Removed 0.1" SWD pins. Reworked pinout.
2020-12-22 Added consealed 0.1mm header for SWD IO and CLK.
2021-05-08 Removed rpi-isl83485 and rpi-isl83488 boards.
    Addresses issue #14.
2021-05-08 Removed ft221x board.
    Addresses issue #15.
2021-05-08 Updated updated symbol Connector:USB_B_Micro.
2021-05-09 Removed PA14, PA15. If needed, remove X1 and bodge to pads.
    Shortened board by 2 rows.
    Added castillated edges.
    Added 0.1" SWD header.
    Put 0.05" SWD header on bottom of board.
    Addresses issue #11.
2021-05-09 Incremented version to 2021-01.
    Fixed 1.2mm castellation.
2021-05-09 Incremented layout to revision 2021-01.
2021-05-09 Updated pinout to add PMOD and VCCIOA/B options.
    * Added castillated pads.
    * Length matched IOs (20mm)
    * ... and more!
2021-05-10 Starting ecp5-stamp.
2021-05-10 Added xesscorp/KiCad-Schematic-Symbol-Libraries to README.
2021-05-11 Finished routing.
    * Not sure what to do with BOOTSEL.
    * Not sure if JTAG header is adequite.
    * Not sure if should route dpairs equal length/together.
    * etc.
2021-05-11 Added 2v5 decoupling caps.
2021-05-12 Tweaked and fixed signal and power traces.
2021-05-15 Committing before branch.
2021-08-22 Added dependencies as git submodules.
2021-08-22 Added xesscorp/KiCad-Schematic-Symbol-Libraries as a git submodule.
2021-08-22 Fixed README enumeration.
    Fixes issue #17.
2021-08-22 Added ecp5-stamp to README.
